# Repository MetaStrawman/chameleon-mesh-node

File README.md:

# Chameleon Mesh Node

> A rugged, dual-radio environmental telemetry node built on the Meshtastic + LoRa stack.

**Submission:** Seeed Studio Meshtastic Build-Off 2026
**Status:** Design complete & verified — routed, DRC-clean (0 errors / 0 unconnected; 31 cosmetic silkscreen/DFM warnings), Gerbers exported. **Pre-fabrication** (first article not yet ordered).
**Hardware revision:** v1.2
**License:** Multi-license open source — CERN-OHL-S-2.0 (hardware), GPL-3.0-or-later (Meshtastic firmware variant), MIT (tooling). See [`LICENSE`](LICENSE) and [`NOTICE.md`](NOTICE.md).

*3D render (top). Bottom: [`assets/chameleon_mesh_node_v1_bottom.png`](assets/chameleon_mesh_node_v1_bottom.png).*

## What it is

The Chameleon Mesh Node is a single-board, USB-powered field appliance for Meshtastic telemetry. It joins a Meshtastic mesh on sub-GHz LoRa for resilient long-range messaging, reads local environment with an on-board sensor, and exposes a Wi-Fi / BLE side-channel for short-range provisioning and bulk-data offload.

Designed as a compact, regenerable two-radio Meshtastic reference board.

## Why dual radio

Most off-the-shelf Meshtastic nodes pick one path: a LoRa-only board that needs a phone to provision, or a Wi-Fi-only "smart sensor" that needs an AP within range. Neither survives a real off-grid deployment where the closest infrastructure is hours away.

This board pairs **two complementary radio subsystems on one PCB**:

| Subsystem | Role | Module |
|---|---|---|
| Long-range mesh | Meshtastic LoRa + GNSS time-sync + Wi-Fi scan for opportunistic uplink | Seeed **Wio-WM1110** (Semtech LR1110 + Nordic nRF52840) |
| Local-area + provisioning | Wi-Fi 6 / BLE 5 / 802.15.4 for setup, OTA, and bulk data offload to a passing operator's phone | Seeed **XIAO ESP32-C5** |

Both radios cohabit one 60×34 mm 2-layer board, with explicit RF zoning and a shared ground pour designed to keep mutual desense within acceptable limits for an environmental-sensing-class duty cycle.

## Top-level specs

| | |
|---|---|
| Dimensions | 60 × 34 mm, 2-layer FR-4 |
| MCU | Nordic nRF52840 (Meshtastic firmware host) + Espressif ESP32-C5 (companion) |
| Radios | Semtech LR1110 (sub-GHz LoRa, GNSS, passive Wi-Fi scan); Wi-Fi 6 / BLE 5 / 802.15.4 |
| Power input | USB-C 5 V (XIAO ESP32-C5 onboard port) |
| Environmental sensor | Bosch BME280 (temperature, humidity, barometric pressure, I²C) |
| Operating temperature | -20 °C to +60 °C (designed; pending environmental test) |

## Repository layout

```
chameleon_mesh_node/
├── README.md                — this file
├── LICENSE                  — multi-license map (see also LICENSES/, NOTICE.md)
├── LICENSES/                — full license texts (CERN-OHL-S-2.0, GPL-3.0, MIT)
├── NOTICE.md                — third-party attribution
├── SUBMISSION_CHECKLIST.md  — Build-Off submission readiness gate
├── assets/                  — 3D renders
├── docs/
│   ├── architecture.md      — block diagram, radio zoning, antenna feeds
│   ├── build-guide.md       — BOM, assembly notes, first-power-on checklist
│   └── power-design.md      — USB-C power input and module power tree
├── hardware/
│   ├── kicad/               — KiCad 10 project (schematic, PCB, footprints, gerber zips)
│   ├── gerbers/             — extracted v1.2 Gerbers + Excellon drill (fab-ready)
│   └── scripts/             — Python composers that regenerate schematic + PCB from source
├── firmware/                — Meshtastic nRF52840 variant (variant.h + platformio.ini) + ESP32-C5 stub
└── enclosure/cad/           — 3D-printable case (planned, post-fab)
```

The KiCad project is fully regenerable: `python3 hardware/scripts/build_schematic.py` rebuilds the schematic from the Python composer, and `python3 hardware/scripts/build_pcb.py` rebuilds the pre-placed PCB. You can wipe the `.kicad_*` files and reproduce the design from source.

## How it uses Meshtastic

The Chameleon Mesh Node **is a Meshtastic node.** The Nordic nRF52840 core of the
Wio-WM1110 runs the [Meshtastic firmware](https://github.com/meshtastic/firmware);
the Semtech LR1110 is its sub-GHz LoRa radio (plus GNSS time-sync and passive
Wi-Fi scan). It joins a Meshtastic mesh, announces itself, relays messages, and
publishes its BME280 environmental readings as Meshtastic telemetry — provisioned
over BLE with the standard Meshtastic mobile app.

Because the base board (Seeed Wio-WM1110 / nRF52840 + LR1110) is already supported
upstream, this project ships as an **incremental hardware variant**, not a new port.
The board-specific deltas (BME280 at I²C `0x76`, an ESP32-C5 companion-wake GPIO)
are captured in [`firmware/variant.h`](firmware/variant.h) +
[`firmware/platformio.ini`](firmware/platformio.ini), layered on the upstream
Wio-WM1110 build environment. See [`firmware/README.md`](firmware/README.md).

## Design state & verification

- Schematic ERC: **0 errors / 0 warnings** (KiCad 10).
- PCB: 2-layer routed (top-copper signal, bottom-copper VBUS detour with vias), 3 GND zones poured, RF-zoned placement.
- Post-route DRC: **0 errors / 0 unconnected / 31 warnings** (cosmetic silkscreen-over-pad, silk-to-edge, library-footprint, and one dangling-track advisory; non-blocking for fabrication — see `docs/design-rationale.md`).
- Gerbers + Excellon drill exported (`hardware/gerbers/`).
- v1.1 → v1.2: top edge truncated 60×40 → 60×34 mm so the USB-C mouth is flush with the board edge (the earlier board had the connector inset and the cable could not seat); the DNP BQ24074 charger (U1) and the LiPo connector (J2) were deleted (their dead VBAT traces shorted the relocated mounting hole), leaving the board USB-powered only; mounting holes relocated, routing and GND zones refilled.

## Status

The board is **design-complete and verified** — schematic + ERC clean, RF-zoned
placement, routing and ground pour done, DRC clean (0 errors / 0 unconnected), and
the full fabrication package (gerbers, drill, BOM, placement, schematic PDF, 3D
renders) is exported and committed. This revision is fab-ready.

**Next:** first-article prototype, board bring-up (power smoke test, Meshtastic
flash over SWD, mesh-join test), deep-sleep current measurement, upstreaming the
Meshtastic variant, and an enclosure design.

## License

Multi-license open source — see [`LICENSE`](LICENSE) for the per-component map and
[`LICENSES/`](LICENSES/) for full texts. Hardware: **CERN-OHL-S-2.0**. Meshtastic
firmware variant: **GPL-3.0-or-later**. Tooling/generators: **MIT**. Third-party
components retain their upstream licenses ([`NOTICE.md`](NOTICE.md)).

## Acknowledgments

- **Seeed Studio** for the Wio-WM1110 module, the XIAO ESP32-C5, and the Meshtastic Build-Off platform
- The **Meshtastic** project for the firmware and the mesh protocol
- **Semtech**, **Nordic**, **Espressif**, **Bosch** for the silicon
- **KiCad** for the EDA toolchain (v10.0.3 used)

## Contact

See repository issues for design questions, build reports, or fork notifications.

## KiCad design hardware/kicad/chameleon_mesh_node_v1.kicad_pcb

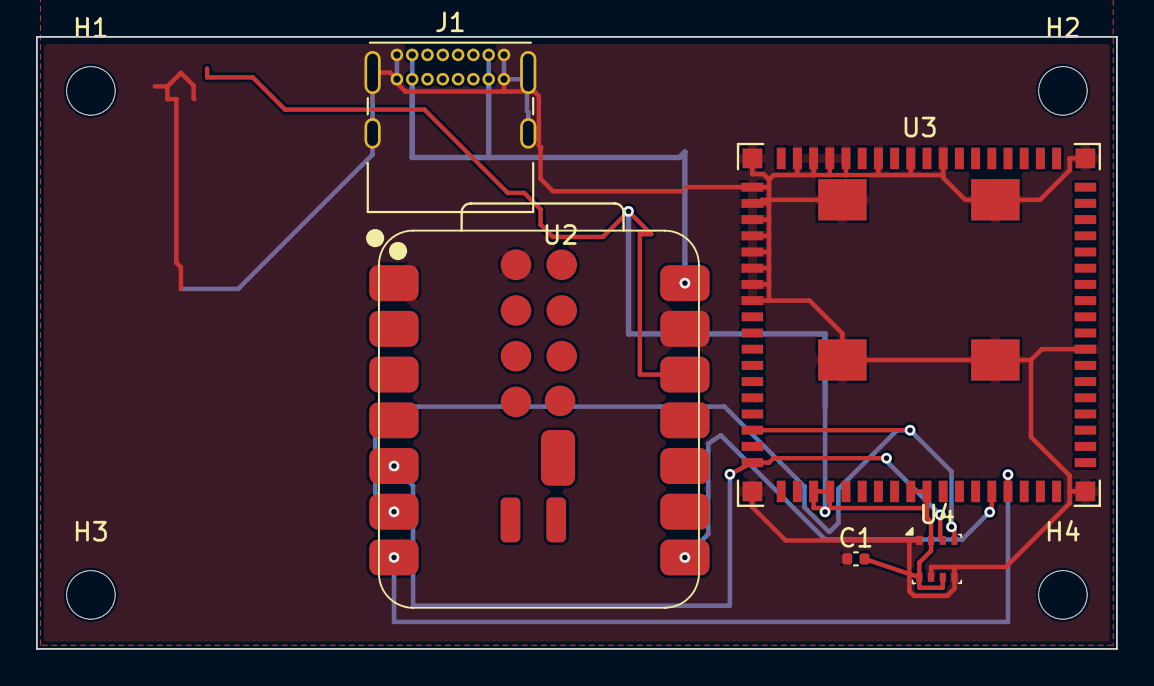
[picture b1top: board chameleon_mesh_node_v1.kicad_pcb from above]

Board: 2 copper layers, 60.0 x 34.0 mm, 9 parts (0 on the bottom side), 7 nets.

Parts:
C1: 100nF; C_0402_1005Metric
H1, H2, H3, H4: M2.5; MountingHole_M2.5
J1: USB-C Power+Data; USB_C_Receptacle_GCT_USB4085
U2: XIAO-ESP32-C5-SMD
U3: Wio-WM1110; Wio_WM1110_LGA80
U4: BME280; Bosch_LGA-8_2.5x2.5mm_P0.65mm_ClockwisePinNumbering

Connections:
+3V3: C1.2, U2.12, U3.21, U3.22, U3.27, U3.28, U4.2, U4.6, U4.8
GND: C1.1, J1.A1, J1.A12, J1.B1, J1.B12, J1.SH, U2.1, U2.13, U2.15, U3.1, U3.2, U3.3, U3.4, U3.5, U3.6, U3.7, U3.8, U3.44, U3.62, U3.64, U3.66, U3.68, U3.69, U3.70, U3.71, U3.73, U3.74, U3.75, U3.76, U3.77, U3.78, U3.79, U3.80, U4.1, U4.5, U4.7
I2C_SCL: U2.6, U3.16, U4.4
I2C_SDA: U2.5, U3.18, U4.3
UART_BRIDGE_RX: U2.8, U3.32
UART_BRIDGE_TX: U2.7, U3.33
VBUS: J1.A4, J1.A9, J1.B4, J1.B9, U2.14

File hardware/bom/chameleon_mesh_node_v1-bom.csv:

"Refs","Value","Footprint","Qty","DNP"
"J1","USB-C Power+Data","Connector_USB:USB_C_Receptacle_GCT_USB4085","1",""
"U2","XIAO-ESP32-C5-SMD","Seeed_XIAO:XIAO-ESP32-C5-SMD","1",""
"U3","Wio-WM1110","ChameleonMeshNode_Custom:Wio_WM1110_LGA80","1",""
"U4","BME280","Package_LGA:Bosch_LGA-8_2.5x2.5mm_P0.65mm_ClockwisePinNumbering","1",""
"C1","100nF","Capacitor_SMD:C_0402_1005Metric","1",""

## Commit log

2026-05-31 Chameleon Mesh Node v1.0 — Seeed Meshtastic Build-Off 2026 submission
    Dual-radio off-grid telemetry node: Wio-WM1110 (LoRa + GNSS + BLE) + XIAO ESP32-C5 (Wi-Fi 6 / BLE 5 / 802.15.4), solar/LiPo power. DRC-clean 2-layer board, Gerbers + KiCad source + firmware variant +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
2026-05-31 hardware: v1.1 DRC fix — resolve U2/J1 collision, 0 errors / 0 unconnected
    Reposition U2 (XIAO) clear of the J1 USB-C connector and re-route the affected
    signal/power nets (I2C SDA/SCL, UART bridge TX/RX, +3V3, VBUS) with the GND
    pour left intact, then correct the over-strict intra-connector and hole-edge
    clearance flags. Board now passes DRC at error severity with 0 violations and
    0 unconnected items under JLCPCB 2-layer rules.
    Re-exported gerbers + Excellon drill, regenerated hardware/kicad/gerbers_v11.zip,
2026-06-01 hardware: publish corrected v1.1 60x35 board (USB-C edge fix)
    Replace the 60x40 board + gerbers + renders with the truncated 60x35
    revision that actually fixes the USB-C cable-insertion blocker (board
    top edge moved flush to the receptacle face; H1/H2 relocated inside the
    new outline; GND pour refilled). Regenerated gerbers + Excellon drill +
    3D renders from the corrected board via kicad-cli; README/docs
    reconciled from the old "U2-reposition" narrative to the truncation fix;
2026-06-01 hardware: add BOM + position file + schematic PDF; checklist sync
    Generated hardware/bom/{*-bom.csv,*-pos.csv} and *-schematic.pdf via
    kicad-cli from the OPSEC-clean public source (not the monorepo, which
    carries internal identifiers in title blocks). Closes the missing
    BOM/POS/schematic submission gap. SUBMISSION_CHECKLIST synced: public
    repo + copyright + BOM items marked done.
2026-06-06 hardware: v1.1 USB-powered fab package — verified board (0 shorts), DNP U1/J2
    - Replace stale published board (had 2 shorts / 136 DRC errors) with the
    verified board: 0 unconnected, 0 shorts, fully routed (11 nets, 210 traces,
    2 GND pours); 29 remaining DRC items are benign USB-C-pitch/edge/thermal DFM noise.
    - Regenerate all gerbers + drill from the verified board.
    - Add hardware/kicad/fab_v1.1_usbpwr/: ready-to-fab ZIP, DNP-aware positions,
    top render, and fab README.
2026-06-14 hardware: v1.2 USB-flush board — replace v1.1, add BME280 decoupling
    v1.2 fixes the USB-C-can't-seat defect: the top edge is truncated 60x40 -> 60x34
    so the connector mouth is flush with the board edge. The DNP BQ24074 charger (U1)
    and the LiPo connector (J2) are removed (their dead VBAT traces shorted the
    relocated mounting hole), so the board is USB-powered only. Mounting holes moved
    into the new outline.
    - Added C1, a 100nF 0402 decoupling cap at the BME280 VDD (placed + routed to
2026-06-14 docs: clean up README status, remove internal dev checklist
    Replace the roadmap todo-list with a concise design-complete/verified status plus
    a forward-looking 'next' note (no stale unchecked items). Remove the internal
    submission-readiness checklist. Drop process/tooling and fab-vendor specifics from
    public docs.
